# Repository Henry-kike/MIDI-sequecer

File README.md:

# MIDI-sequecer
***Simple polyphonic MIDI sequencer based in the esp32 with oled display***

I'm looking to combine the best of sequencers like keystep pro and op-1. I make animations for the diferent mode of my sequencer (inspired in the op-1) and i work on adding two track (like keystep pro). The sequencer can save and play chords sequences and i want to add song mode which could play a sequence in different starting notes. Then i will work on playing two sequence simultaneusly, firts on two different MIDI chanels and later in two phisycal MIDI ports.

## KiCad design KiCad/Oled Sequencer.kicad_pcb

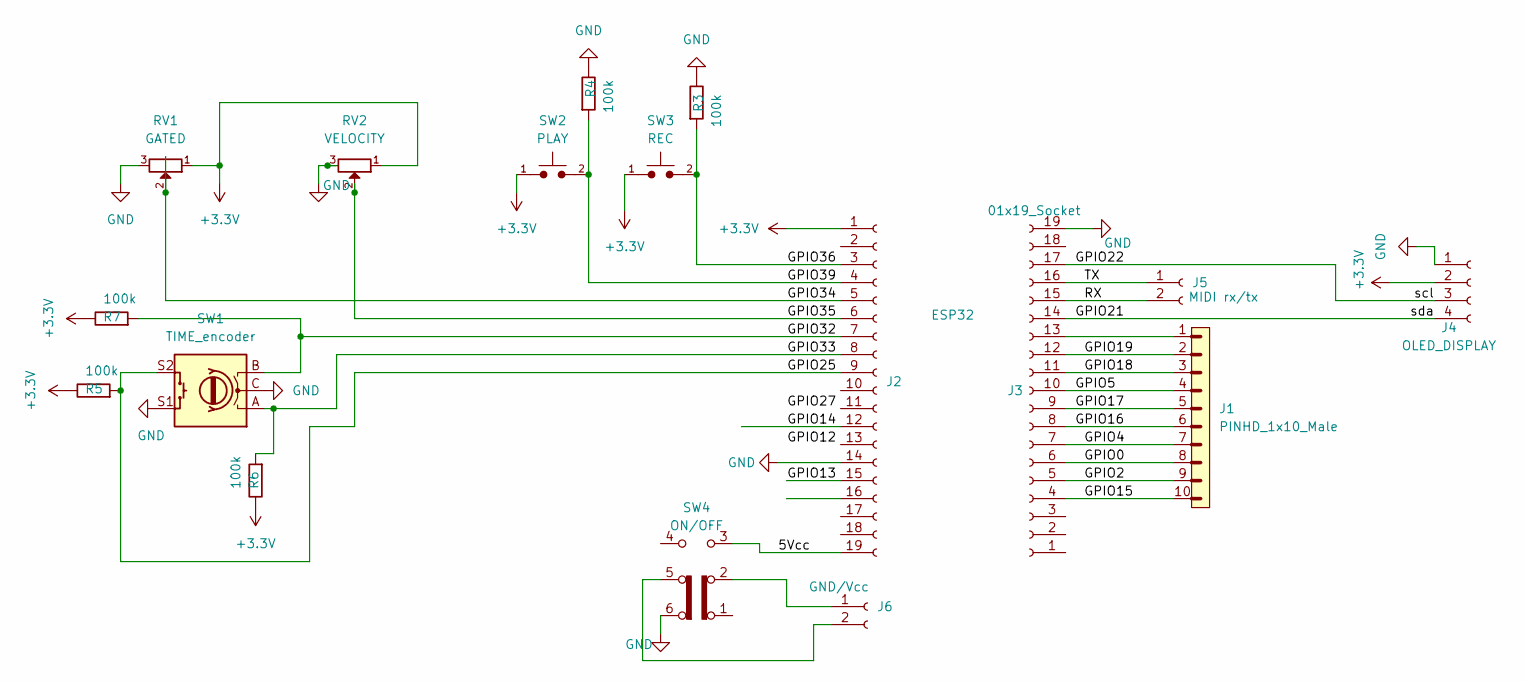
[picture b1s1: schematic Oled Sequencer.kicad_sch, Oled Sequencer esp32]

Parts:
J1: PINHD_1x10_Male; PinHeader_1x10_P2.54mm_Vertical
J2: ESP32; PinSocket_1x19_P2.54mm_Vertical
J3: 01x19_Socket; PinSocket_1x19_P2.54mm_Vertical
J4: OLED_DISPLAY; PinHeader_1x04_P2.54mm_Vertical
J5: MIDI rx/tx; PinHeader_1x02_P2.54mm_Vertical
J6: GND/Vcc; PinHeader_1x02_P2.54mm_Vertical
R3, R4, R5, R6, R7: 100k; R_Axial_DIN0207_L6.3mm_D2.5mm_P10.16mm_Horizontal
RV1: GATED; Potentiometer_Bourns_PTA2043_Single_Slide
RV2: VELOCITY; Potentiometer_Bourns_PTA2043_Single_Slide
SW1: TIME_encoder; RotaryEncoder_Alps_EC11E-Switch_Vertical_H20mm
SW2: PLAY; SW_PUSH_6mm
SW3: REC; SW_PUSH_6mm
SW4: ON/OFF; SW_E-Switch_EG1271_SPDT

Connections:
+3.3V: J2.1, J4.2, R5.2, R6.2, R7.2, RV1.1, RV2.1, SW2.1, SW3.1
/5Vcc: J2.19, SW4.3 (C)
/GPIO0: J1.8, J3.6
/GPIO2: J1.9, J3.5
/GPIO4: J1.7, J3.7
/GPIO5: J1.4, J3.10
/GPIO13: J2.15
/GPIO14: J2.12
/GPIO15: J1.10, J3.4
/GPIO16: J1.6, J3.8
/GPIO17: J1.5, J3.9
/GPIO18: J1.3, J3.11
/GPIO19: J1.2, J3.12
/GPIO21: J3.14, J4.4
/GPIO22: J3.17, J4.3
/GPIO25: J2.9, R5.1, SW1.S2
/GPIO32: J2.7, R7.1, SW1.B
/GPIO33: J2.8, R6.1, SW1.A
/GPIO34: J2.5, RV1.2
/GPIO35: J2.6, RV2.2
/GPIO36: J2.3, R3.1, SW3.2
/GPIO39: J2.4, R4.1, SW2.2
/RX: J3.15, J5.2
/TX: J3.16, J5.1
GND: J2.14, J3.19, J4.1, R3.2, R4.2, RV1.3, RV2.3, SW1.C, SW1.S1, SW4.6 (C)
unnamed: J1.1, J3.13
unnamed: J6.1, SW4.2 (B)
unnamed: J6.2, SW4.5 (B)

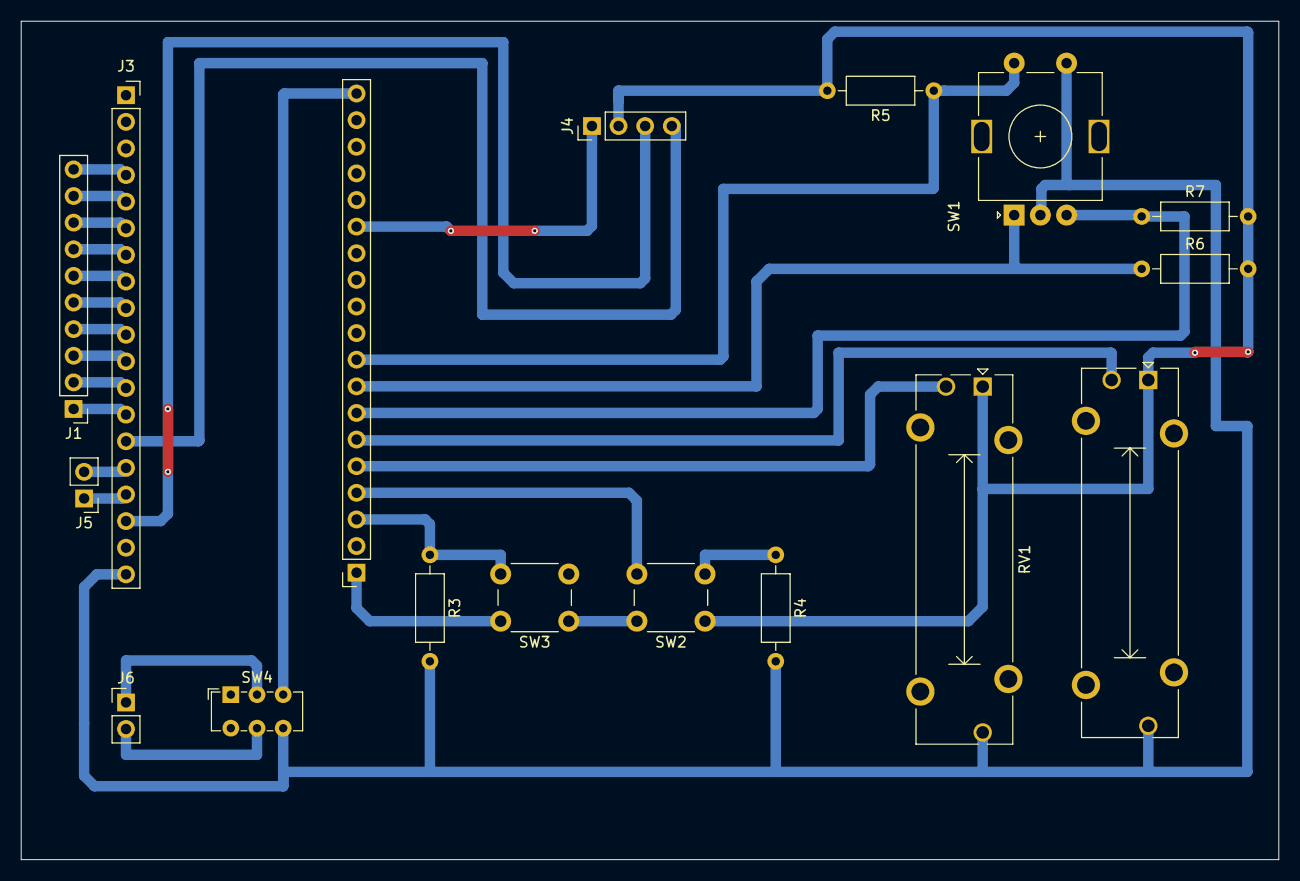
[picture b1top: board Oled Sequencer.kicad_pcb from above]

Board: 2 copper layers, 120.0 x 80.0 mm, 17 parts (0 on the bottom side), 26 nets.

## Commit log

2024-08-15 Create x
